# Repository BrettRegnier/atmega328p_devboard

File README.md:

# atmega328p_devboard
Very simple devboard that puts a atmega328p onto a breadboard with minimal features.

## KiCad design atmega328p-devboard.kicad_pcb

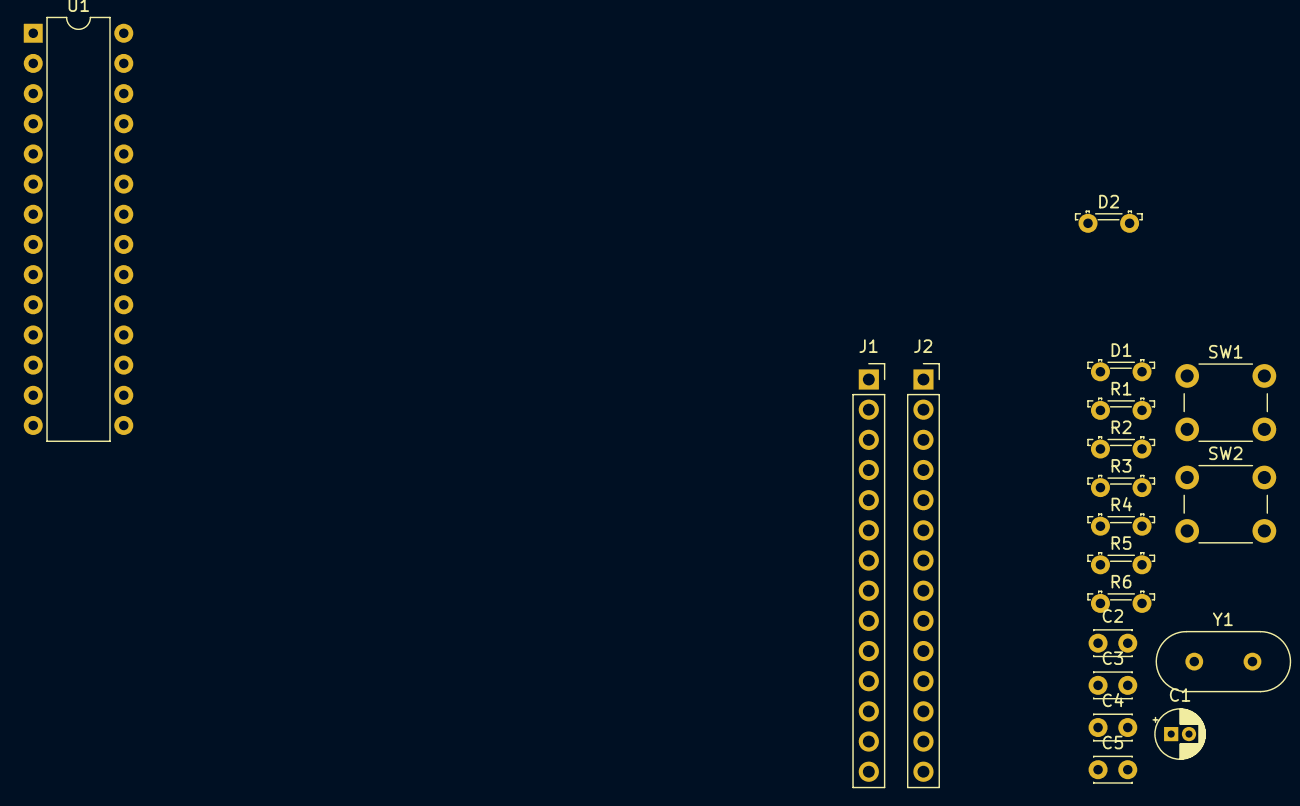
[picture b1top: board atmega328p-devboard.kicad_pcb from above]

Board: 2 copper layers, 19 parts (0 on the bottom side), 9 nets, no tracks yet.

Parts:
C1: 4.7u; CP_Radial_D4.0mm_P1.50mm
C2, C3: 100n; C_Disc_D3.0mm_W2.0mm_P2.50mm
C4, C5: 22p; C_Disc_D3.0mm_W2.0mm_P2.50mm
D1, D2: LED; R_LDR_5.2x5.2mm_P3.5mm_Horizontal
J1, J2: Conn_01x14; PinSocket_1x14_P2.54mm_Vertical
R1, R3, R5, R6: 10k; R_LDR_5.2x5.2mm_P3.5mm_Horizontal
R2, R4: 1k; R_LDR_5.2x5.2mm_P3.5mm_Horizontal
SW1: RESET; SW_PUSH_6mm
SW2: BOOT; SW_PUSH_6mm
U1: ATmega328P-P; DIP-28_W7.62mm
Y1: 16M; Crystal_HC18-U_Vertical

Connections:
/BOOT: R3.2, R4.1, SW2.1, U1.11 (PD5)
/PD2: R6.1, U1.4 (PD2)
/XTAL1: C5.1, U1.9 (XTAL1/PB6), Y1.1
/XTAL2: C4.1, U1.10 (XTAL2/PB7), Y1.2
/nRESET: R1.2, R2.1, SW1.1, U1.1 (~RESET/PC6)
GND: C1.2, C2.2, C3.2, C4.2, C5.2, D1.1 (K), D2.1 (K), SW1.2, SW2.2, U1.8 (GND), U1.22 (GND)
unnamed: D1.2 (A), R5.2
unnamed: D2.2 (A), R6.2
VCC: C1.1, C2.1, C3.1, R1.1, R3.1, R5.1, U1.7 (VCC), U1.20 (AVCC)

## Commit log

2025-04-10 feat: Add start of pcb and sch
